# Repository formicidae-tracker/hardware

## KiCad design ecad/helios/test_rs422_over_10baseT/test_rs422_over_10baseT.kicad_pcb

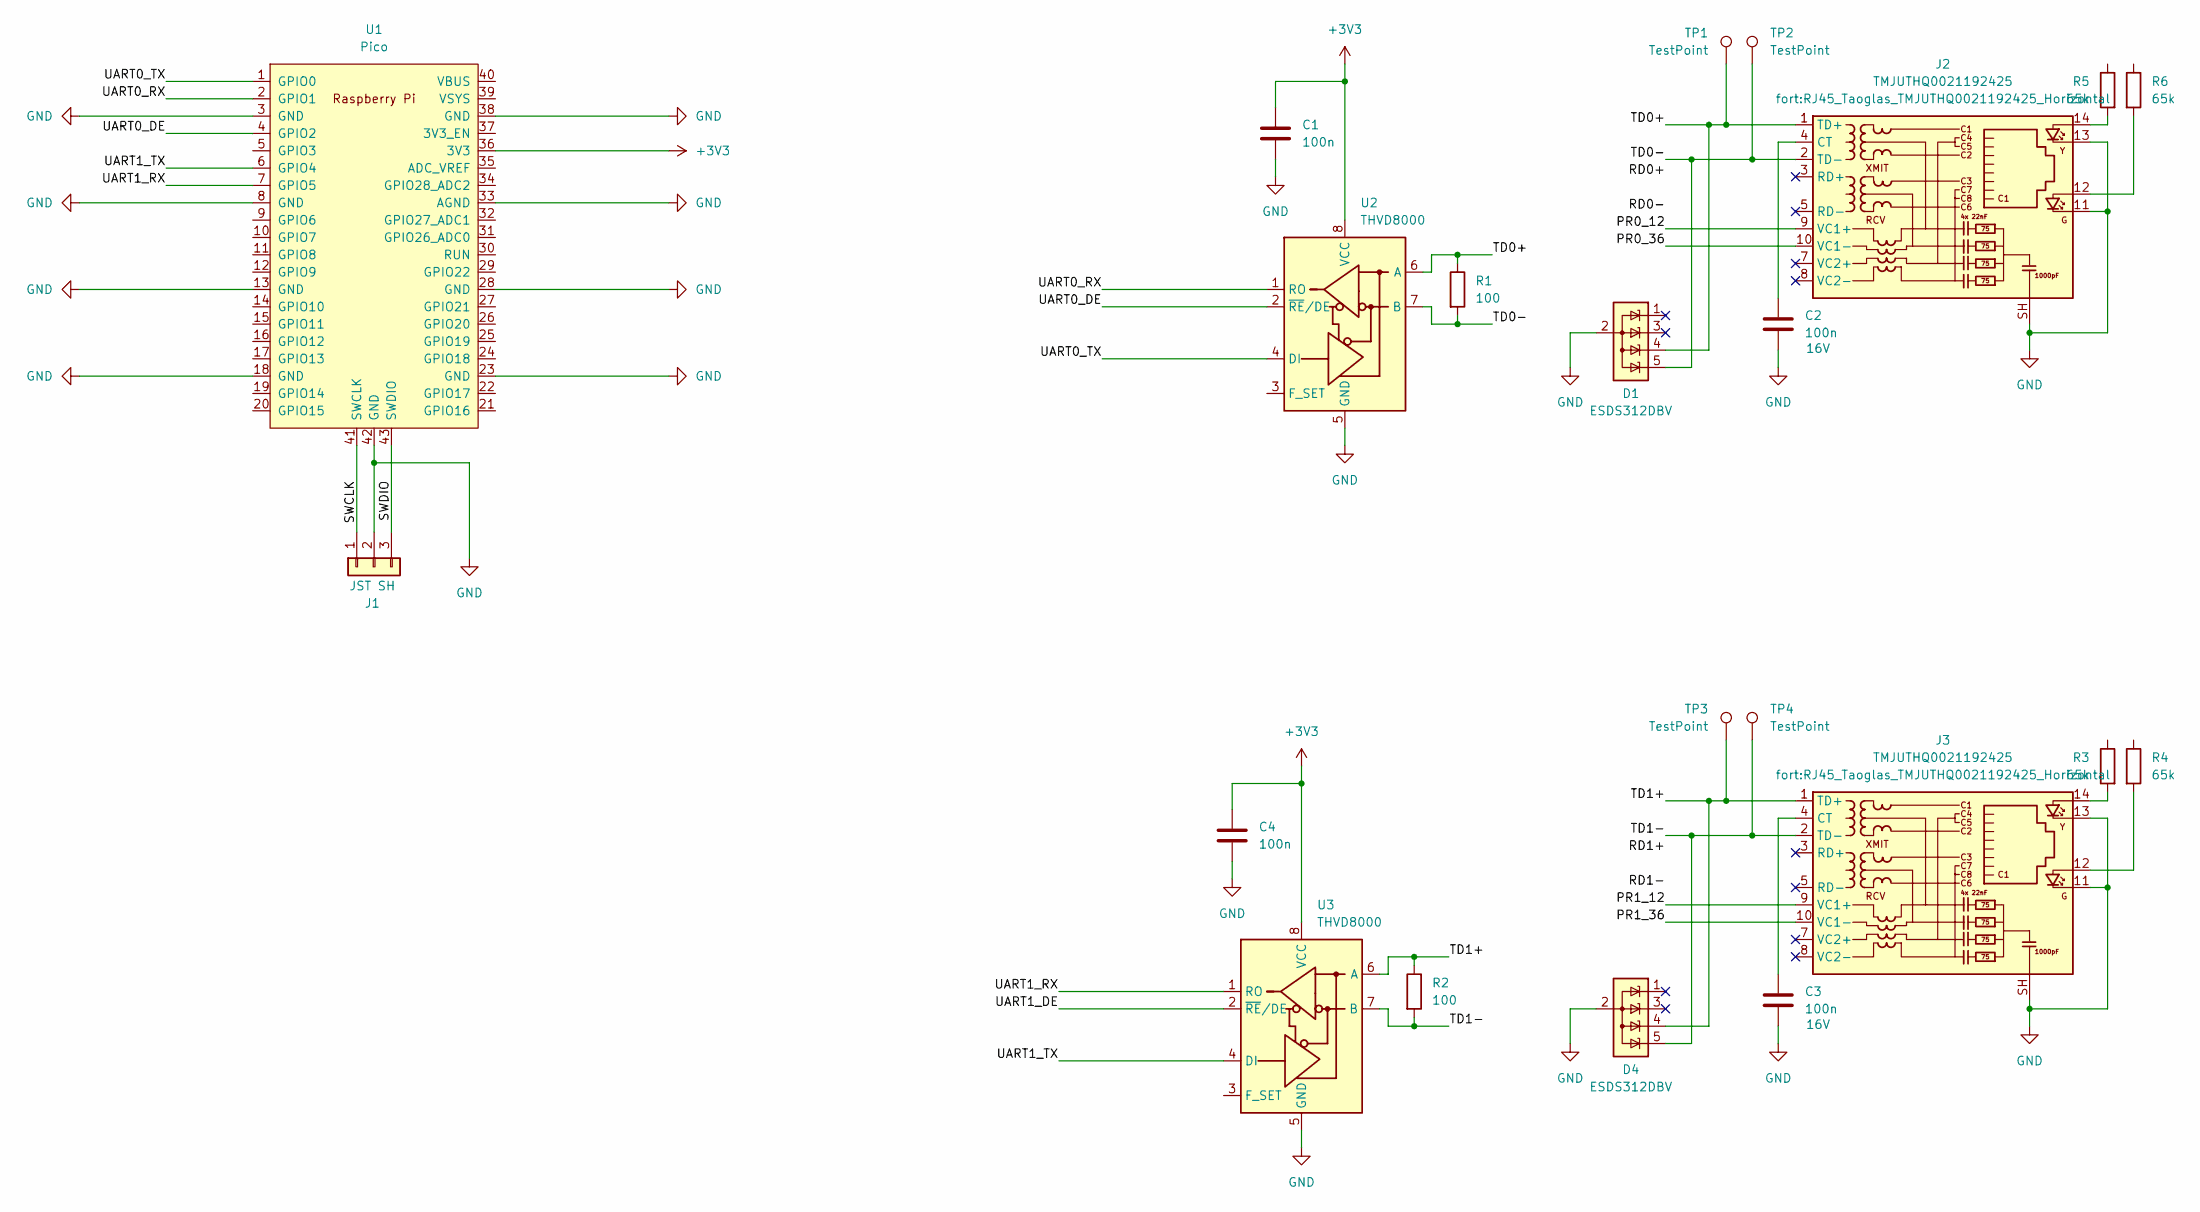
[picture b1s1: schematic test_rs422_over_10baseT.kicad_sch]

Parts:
C1, C4: 100n; C_0402_1005Metric
C2, C3: 100n; C_0402_1005Metric; Rated Voltage 16V
D1, D4: ESDS312DBV; SOT-23-5
J1: JST SH; JST_SH_BM03B-SRSS-TB_1x03-1MP_P1.00mm_Vertical; MPN SM03B-SRSS-TB
J2, J3: TMJUTHQ0021192425; RJ45_Taoglas_TMJUTHQ0021192425_Horizontal
R1, R2: 100; R_0402_1005Metric
R3, R4, R5, R6: 65k; R_0402_1005Metric
TP1, TP2, TP3, TP4: TestPoint; TestPoint_Keystone_5015_Micro-Minature
U1: Pico; RPi_Pico_SMD_TH; MPN SC0915
U2, U3: THVD8000; Texas_SOT-23-8-THIN_1.6x2.9m

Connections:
+3V3: C1.1, C4.1, U1.36 (3V3), U2.8 (VCC), U3.8 (VCC)
/PR0_12: J2.9 (VC1+)
/PR0_36: J2.10 (VC1-)
/PR1_12: J3.9 (VC1+)
/PR1_36: J3.10 (VC1-)
/SWCLK: J1.1, U1.41 (SWCLK)
/SWDIO: J1.3, U1.43 (SWDIO)
/TD0+: D1.4 (K), J2.1 (TD+), R1.1, TP1.1, U2.6 (A)
/TD0-: D1.5 (K), J2.2 (TD-), R1.2, TP2.1, U2.7 (B)
/TD1+: D4.4 (K), J3.1 (TD+), R2.1, TP3.1, U3.6 (A)
/TD1-: D4.5 (K), J3.2 (TD-), R2.2, TP4.1, U3.7 (B)
/UART0_DE: U1.4 (GPIO2), U2.2 (~RE/DE)
/UART0_RX: U1.2 (GPIO1), U2.1 (RO)
/UART0_TX: U1.1 (GPIO0), U2.4 (DI)
/UART1_DE: U3.2 (~RE/DE)
/UART1_RX: U1.7 (GPIO5), U3.1 (RO)
/UART1_TX: U1.6 (GPIO4), U3.4 (DI)
GND: C1.2, C2.2, C3.2, C4.2, D1.2 (A), D4.2 (A), J1.2, J2.11, J2.13, J2.SH, J3.11, J3.13, J3.SH, U1.3 (GND), U1.8 (GND), U1.13 (GND), U1.18 (GND), U1.23 (GND), U1.28 (GND), U1.33 (AGND), U1.38 (GND), U1.42 (GND), U2.5 (GND), U3.5 (GND)
unnamed: C2.1, J2.4 (CT)
unnamed: J2.12, R6.2
unnamed: J2.14, R5.2
unnamed: C3.1, J3.4 (CT)
unnamed: J3.12, R4.2
unnamed: J3.14, R3.2

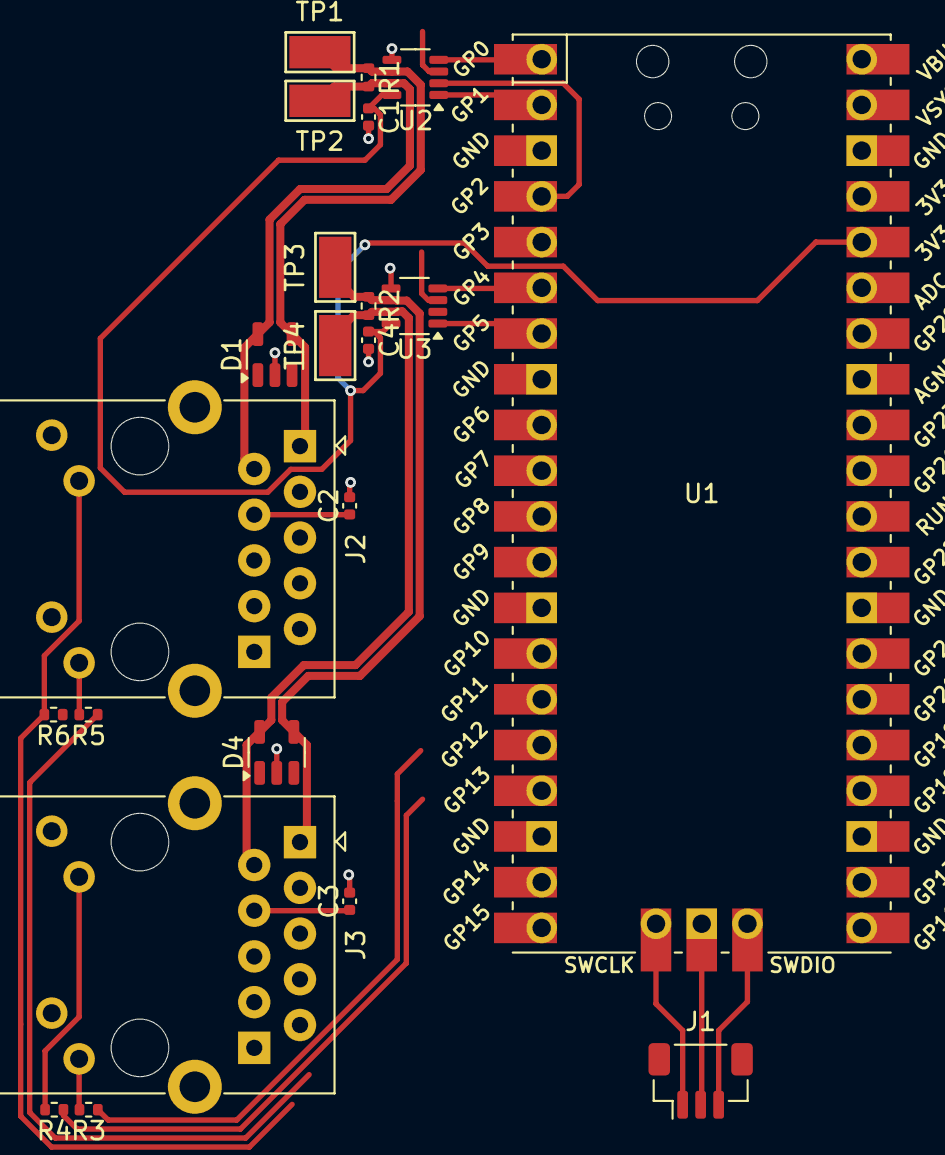
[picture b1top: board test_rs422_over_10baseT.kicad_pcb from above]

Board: 2 copper layers, 22 parts (0 on the bottom side), 19 nets.

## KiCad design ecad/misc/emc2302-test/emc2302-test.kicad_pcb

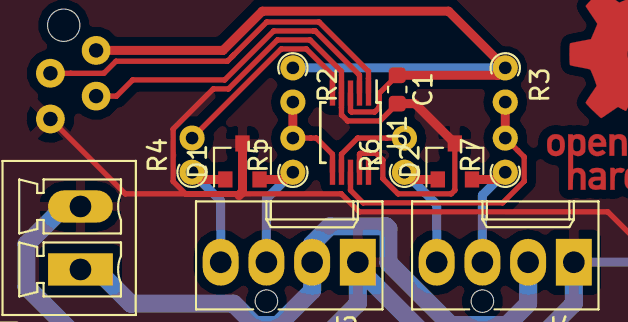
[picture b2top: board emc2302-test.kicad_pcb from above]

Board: 2 copper layers, 14 parts (1 on the bottom side), 13 nets.

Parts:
C1: 100nF; C_0603_1608Metric
D1, D2: CPDT-5V0-HF; SOT-23
J1: Conn_01x02; PhoenixContact_MCV_1,5_2-G-3.5_1x02_P3.50mm_Vertical
J2, J4: Conn_01x04; Molex_KK-47053-04_04x2.54mm_Straight
J3: Conn_01x04; Micro-Match_4_TH
R2, R3: 47k; R_Axial_DIN0204_L3.6mm_D1.6mm_P1.90mm_Vertical
R4, R5, R6, R7: 2k2; R_Axial_DIN0204_L3.6mm_D1.6mm_P1.90mm_Vertical
U1: EMC2302-1-AIZL-TR; MSOP-10_3x3mm_P0.5mm

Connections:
+3V3: C1.1, J3.1, R2.1, R3.1, U1.3
+12V: J1.1, J2.2, J4.2
/Fan Controller/PWM1: D1.1, J2.4, R4.1
/Fan Controller/PWM1_PR: R4.2, U1.5
/Fan Controller/PWM2: D2.1, J4.4, R6.1
/Fan Controller/PWM2_PR: R6.2, U1.7
/Fan Controller/SCL: J3.3, U1.2
/Fan Controller/SDA: J3.2, U1.1
/Fan Controller/TACH1: D1.2, J2.3, R5.1
/Fan Controller/TACH1_PR: R2.2, R5.2, U1.6
/Fan Controller/TACH2: D2.2, J4.3, R7.1
/Fan Controller/TACH2_PR: R3.2, R7.2, U1.8
GND: C1.2, D1.3, D2.3, J1.2, J2.1, J3.4, J4.1, U1.4, U1.9

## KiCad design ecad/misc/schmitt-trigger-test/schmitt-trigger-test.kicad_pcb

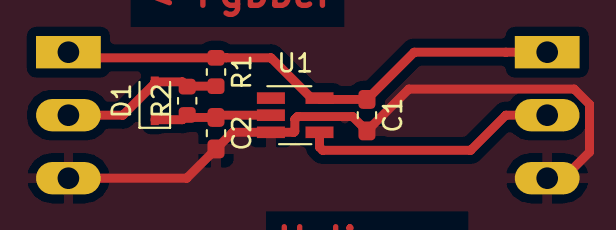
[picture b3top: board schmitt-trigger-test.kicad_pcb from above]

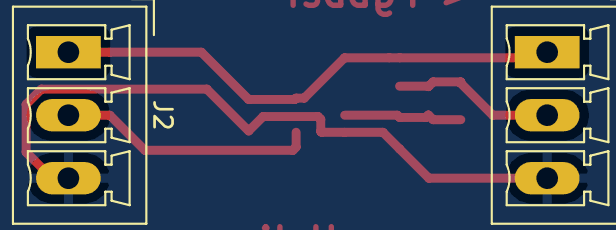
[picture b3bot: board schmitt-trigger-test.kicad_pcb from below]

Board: 2 copper layers, 8 parts (2 on the bottom side), 5 nets.

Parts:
C1: C; C_0603_1608Metric_Pad1.05x0.95mm_HandSolder
C2: 1nF; C_0603_1608Metric_Pad1.05x0.95mm_HandSolder
D1: 1N4148WS; D_SOD-323
J1, J2: Conn_01x03; PhoenixContact_MCV_1,5_3-G-3.5_1x03_P3.50mm_Vertical
R1, R2: 10k; R_0603_1608Metric
U1: 74LVC1G17; SOT-23-5_HandSoldering

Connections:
/Filtered: J2.2, U1.4
/RAW: D1.2, J1.2, R1.2, R2.2
GND: C1.2, C2.2, J1.3, J2.3, U1.3
unnamed: C2.1, D1.1, R2.1, U1.2
VCC: C1.1, J1.1, J2.1, R1.1, U1.5
